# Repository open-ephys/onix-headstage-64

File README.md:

# ONIX 64-Channel Headstage
Serialized, multifunction headstage for wire electrode or silicon probe recordings.

- 64x electrophysiology channels
- 3x auxiliary analog channels (1x used by for stimulation current loop-back by
  default)
- 2x optical stimulation channels (LEDs or laser diodes; 800 mA per channel)
- 1x electrical stimulator (±2.5 mA, ±15V compliance; automatic discharge circuit)
- Integrated real-time, room-scale 3D-position tracking
- Integrated absolute orientation tracking

<br>
<br>

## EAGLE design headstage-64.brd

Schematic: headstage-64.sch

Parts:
C1: 0.1uF; 0201T; PARTNP CL03A104KA3NNNC
C2, C3, C5, C6, C18, C27, C32, C33, C35: 0.1uF; 0201T; PARTNO C0603X5R1C104K030BC
C4, C8, C9: 0.1uF; 0201T; PARTNO CL03A104KA3NNNC
C7: 4.7uF; 0402T; PARTNO CL05A475MO5NUNC
C10, C14, C15, C21, C22, C45, C51, C59, C66, C71: 10nF; 0201T
C11, C13, C16, C20, C23, C30, C31, C48: 0.1uF; 0201T
C12, C17: 4.7uF; 0402T; PARTNO GRM155R61A475MEAAD
C19, C28, C34, C36, C49: 1uF; 0201T; PARTNO CL03A105MP3ZSNH
C24: 15uF; 0402T; PARTNO CL05A226MQ5QUNC
C25: 0.1uF; 0201T; PARTNO C1005X7R1H104K050BB
C26: 47nF; 0201T; PARTNO C1005X7R1H473K050BB
C29: 10nF; 0201T; PARTNO GRM033R71E103KE14D
C37, C39, C41, C55, C69: 10uF; 0402T; PARTNO CL05A105KO5NNNC
C38, C40, C54, C56: 10uF; 0402T; PARTNO CL05A106MQ5NUNC
C42, C64: 0.22uF; 0402T; PARTNO UMK105BJ224KV-F
C43: 2.2nF; 0201T
C44, C50, C58, C65: 4.7nF; 0201T
C46, C52, C60, C67: 22nF; 0201T
C47, C61: 47nF; 0201T
C53, C62, C68: 0.47uF; 0201T; PARTNO GRM033R60J474KE90D
C57: 10pF; 0201T
C63, C72: 1uF; 0402T; PARTNO CL05A105KO5NNNC
C70: 4.7uF; 0402T; PARTNO CL05A105KO5NNNC
C73: 15uF; 0402T; PARTNO CL05A226MQ6ZUN8
C74, C75, C77: 10uF; 0402T; PARTNO CL05A475MO5NUNC
D4, D5, D6, D8: VEMD1160X01; 0805PT
D7: XZVGR155W; LED-0201T
D9: VSKY05401006; CLP1006-2L
J5: PINHD-1X4HEADSTAGE64_DAUGHTER-CARD; HEADSTAGE-64-DAUGHTER-CARD
J8: DF40C-70DP-0.4V(51); DF40-70HEAD-LESS-SILK
J9: PINHD-1X5_HALF_CONNECTOR; DF40-10HEAD_HALF
L2: BLM18KG601SN1D; 0603T
L4: CBC3225T101MR; 1210T
L6, L7, L8, L10: BLM15PX601SN1D; 0402T; PARTNO BLM15PX601SN1D
L9, L11: MLZ2012M100WT000; 0805T
L12: LQM21PN1R0NGRD; 0805T
R1: 9k, 0.1%; 0201T
R2: 1k, 0.1%; 0201T
R4, R5, R6, R7, R8, R11, R14, R16, R17, R18, R19: 10k, 0.1%; 0201T
R10, R21, R43: 1k; 0201T
R12, R31, R34, R35, R47: 100; 0201T
R13: 2.86k; 0201T
R15: 590; 0201T
R22, R23, R27, R28, R32, R33, R38, R39, R40, R49, R53, R54, R55, R56, R57: 10k; 0201T
R24, R26, R36, R42: 15k; 0201T
R25: 49.9; 0201T
R29: 0; 0201T
R30: 100k; 0201T
R37: 2k; 0201T
R41, R44, R51, R52: 4.7k; 0201T
R45, R50: 1M; 0201T
R46: 90.9k; 0201T
R48: 83.3k; 0201T
TP1, TP2, TP5, TP6: VCC; TP07R
TP3, TP4: TPTP09R; TP09R
TP7, TP8, TP9, TP10, TP11, TP12, TP13: TPTP06R; TP06R
TP14: gnd; TP06R
TP15: VCC; TP06R
U1: ADA4062-4ACPZ-R7; CP_16_27-L
U2: AD5681RBCPZ-1RL7; CP_8_10-L
U3: CAT4016_QFN; QFN24-4X4; PARTNO CAT4016HV6-GT2
U4: TPL0501_UQFN; UQFN; PARTNO TPL0501-100RSER
U5: DG509B; MQFN16-1.8X2.6
U6, U8, U11, U12: TS4231; WLCSP3X3
U7: RHD2064_BGA; BGA104_0.5MM
U9: DS90UB913A_WQFN; WQFN32-5X5
U10: BNO055; LGA-28-3.8X5.2
U13, U15: TLV70733; X2SON
U14: 10M08DC; VBGA81-4X4
U16: LT3463; DFN103X3
U17: TLV70725; X2SON
U18: TPS62621; XBGA6_1.2X0.8
U19: ASCO-50.000MHZ-EK-T3; ASCO
U20: TLV70712; X2SON

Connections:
!IMU_BL: R28.2, U10.4 (!BOOT_LOAD)
!IMU_RESET: R32.1, U10.11 (!RESET)
$N324: C50.1, C51.1, C52.1, C53.1, C54.1, L10.2, U14.A8 (VCCD_PLL2)
+1V2: C43.1, C44.1, C45.1, C46.1, C47.1, C48.1, C49.1, C73.1, L10.1, U14.B2 (VCC), U14.B9 (VCC), U14.H2 (VCC), U14.H8 (VCC), U20.1 (OUT)
+1V8: C13.1, C14.1, C15.1, C16.1, C17.1, C70.1, L6.1, L8.1, L12.1, R27.1, U9.11 (VDDT), U9.28 (VDDD), U18.C1 (FB)
+2V5: C56.1, C65.1, C66.1, C67.1, C68.1, C72.1, U14.B1 (VCCA3), U14.B8 (VCCA2), U14.J1 (VCCA1), U14.J9 (VCCA4), U17.1 (OUT), U20.3 (EN), U20.4 (IN)
+3V3: C3.1, C5.1, C18.1, C20.1, C21.1, C27.1, C31.1, C32.1, C35.1, C40.1, C58.1, C59.1, C60.1, C61.1, C62.1, C71.1, R22.1, R28.1, R32.2, R33.1, R37.1, R38.1, R39.1, R40.1, R41.2, R44.1, R51.2, R52.1, R53.1, R54.1, R55.1, R56.1, TP14.TP, U2.2 (VLOGIC), U4.7 (VDD), U6.C3 (DVDD), U8.C3 (DVDD), U9.25 (VDDIO), U10.3 (VDD), U10.28 (VDDIO), U11.C3 (DVDD), U12.C3 (DVDD), U14.D5 (VCCIO8), U14.E4 (VCCIO1_2), U14.E6 (VCCIO5_6), U14.F5 (VCCIO3), U15.1 (OUT), U19.1 (EN), U19.4 (VCC)
+3V3_AN: C30.2, C38.1, J9.4 (5), U7.M15 (VDD), U7.M16 (LVDS_EN), U7.N2 (VDD), U7.N15 (VDD), U13.1 (OUT)
+15V0: C1.1, C8.1, C42.1, R45.2, U1.3 (V+), U5.12 (V+), U16.1 (VOUT1)
-15V0: C4.1, C9.1, C57.2, C64.1, D9.A, R50.1, U1.10 (V-), U1.PAD (V-), U5.1 (V-)
AGND: C29.2, C30.1, C37.2, C38.2, J8.70, J8.M1, J8.M2, J8.M4, J9.M1 (1), J9.M2 (6), L7.2, R29.1, TP1.TP, U7.M2 (VESD), U7.M17 (GND), U7.N1 (GND), U7.N6 (GND), U13.2 (GND), U13.PAD (GND)
AUXIN2: J9.2 (3), TP6.TP, U7.N4 (AUXIN2)
AUXIN3: J9.1 (2), TP5.TP, U7.N3 (AUXIN1)
CONFIG_SEL: R57.1, U14.C6 (CONFIG_SEL/C6)
CONF_DONE: R56.2, U14.A2 (DIFFIO_RX_T24N/CONF_DONE/A2)
DAC_CS: U2.5 (!SYNC), U14.A5 (DIFFIO_RX_T18N/A5)
DATA1: U6.C1 (D/CFGDATA), U14.C7 (DIFFIO_RX_R33P/PLL_R_CLKOUTP/C7)
DATA2: U8.C1 (D/CFGDATA), U14.C3 (DIFFIO_RX_T26N/C3)
DATA3: U11.C1 (D/CFGDATA), U14.A7 (DIFFIO_RX_T16P/A7)
DATA4: U12.C1 (D/CFGDATA), U14.B6 (DIFFIO_RX_T16N/DEV_CLRN/B6)
DIN0: U9.19 (DIN0), U14.J6 (DIFFIO_TX_RX_B12P/J6)
DIN1: U9.20 (DIN1), U14.G6 (DIFFIO_TX_RX_B14N/G6)
DIN2: U9.21 (DIN2), U14.H7 (DIFFIO_TX_RX_B14P/H7)
DIN3: U9.22 (DIN3), U14.J7 (DIFFIO_TX_RX_B16N/J7)
DIN4: U9.23 (DIN4), U14.G8 (DIFFIO_RX_R7P/G8)
DIN5: U9.24 (DIN5), U14.G9 (DIFFIO_RX_R7N/G9)
DIN6: U9.26 (DIN6), U14.F7 (DIFFIO_RX_R1N/F7)
DIN7: U9.27 (DIN7), U14.E7 (DIFFIO_RX_R14N/CLK2N/E7)
DIN8: U9.29 (DIN8), U14.E8 (DIFFIO_RX_R14P/CLK2P/E8)
DIN9: U9.30 (DIN9), U14.C8 (DIFFIO_RX_R27P/C8)
DIN10: U9.31 (DIN10), U14.C5 (CRC_ERROR/C5)
DIN11: U9.32 (DIN11), U14.C4 (DIFFIO_RX_T26P/C4)
E0: J8.2, U7.K2 (IN0)
E1: J8.68, U7.J1 (IN1)
E2: J8.3, U7.J2 (IN2)
E3: J8.67, U7.H1 (IN3)
E4: J8.4, U7.H2 (IN4)
E5: J8.66, U7.G1 (IN5)
E6: J8.5, U7.G2 (IN6)
E7: J8.65, U7.F1 (IN7)
E8: J8.6, U7.F2 (IN8)
E9: J8.64, U7.E1 (IN9)
E10: J8.7, U7.E2 (IN10)
E11: J8.63, U7.D1 (IN11)
E12: J8.8, U7.D2 (IN12)
E13: J8.62, U7.C1 (IN13)
E14: J8.9, U7.C2 (IN14)
E15: J8.61, U7.B1 (IN15)
E16: J8.10, U7.A1 (IN16)
E17: J8.60, U7.B2 (IN17)
E18: J8.11, U7.A2 (IN18)
E19: J8.59, U7.B3 (IN19)
E20: J8.12, U7.A3 (IN20)
E21: J8.58, U7.B4 (IN21)
E22: J8.13, U7.A4 (IN22)
E23: J8.57, U7.B5 (IN23)
E24: J8.14, U7.A5 (IN24)
E25: J8.56, U7.B6 (IN25)
E26: J8.15, U7.A6 (IN26)
E27: J8.55, U7.B7 (IN27)
E28: J8.16, U7.A7 (IN28)
E29: J8.54, U7.B8 (IN29)
E30: J8.17, U7.A8 (IN30)
E31: J8.53, U7.B9 (IN31)
E32: J8.18, U7.A9 (IN32)
E33: J8.52, U7.A10 (IN33)
E34: J8.19, U7.B10 (IN34)
E35: J8.51, U7.A11 (IN35)
E36: J8.20, U7.B11 (IN36)
E37: J8.50, U7.A12 (IN37)
E38: J8.21, U7.B12 (IN38)
E39: J8.49, U7.A13 (IN39)
E40: J8.22, U7.B13 (IN40)
E41: J8.48, U7.A14 (IN41)
E42: J8.23, U7.B14 (IN42)
E43: J8.47, U7.A15 (IN43)
E44: J8.24, U7.B15 (IN44)
E45: J8.46, U7.A16 (IN45)
E46: J8.25, U7.B16 (IN46)
E47: J8.45, U7.A17 (IN47)
E48: J8.26, U7.B17 (IN48)
E49: J8.44, U7.C16 (IN49)
E50: J8.27, U7.C17 (IN50)
E51: J8.43, U7.D16 (IN51)
E52: J8.28, U7.D17 (IN52)
E53: J8.42, U7.E16 (IN53)
E54: J8.29, U7.E17 (IN54)
E55: J8.41, U7.F16 (IN55)
E56: J8.30, U7.F17 (IN56)
E57: J8.40, U7.G16 (IN57)
E58: J8.31, U7.G17 (IN58)
E59: J8.39, U7.H16 (IN59)
E60: J8.32, U7.H17 (IN60)
E61: J8.38, U7.J16 (IN61)
E62: J8.33, U7.J17 (IN62)
E63: J8.37, U7.K16 (IN63)
ENV1: U6.C2 (E/CFGCLK), U14.B5 (DIFFIO_RX_T19N/B5)
ENV2: U8.C2 (E/CFGCLK), U14.C2 (DIFFIO_RX_L1N/C2)
ENV3: U11.C2 (E/CFGCLK), U14.D9 (DIFFIO_RX_R16N/CLK3N/D9)
ENV4: U12.C2 (E/CFGCLK), U14.B7 (DIFFIO_RX_R33N/PLL_R_CLKOUTN/B7)
ESTIM_POW_EN: R49.1, U14.A6 (DIFFIO_RX_T18P/DEV_OE/A6), U16.8 (!SHDN2), U16.9 (!SHDN1)
GND: C1.2, C2.2, C3.2, C4.2, C5.2, C6.2, C7.2, C8.2, C9.2, C10.2, C11.2, C12.2, C13.2, C14.2, C15.2, C16.2, C17.2, C18.2, C19.2, C20.2, C21.2, C22.2, C23.2, C24.2, C27.2, C28.2, C31.2, C32.2, C33.1, C34.2, C35.2, C36.2, C39.2, C40.2, C41.2, C42.2, C43.2, C44.2, C45.2, C46.2, C47.2, C48.2, C49.2, C50.2, C51.2, C52.2, C53.2, C54.2, C55.2, C56.2, C58.2, C59.2, C60.2, C61.2, C62.2, C64.2, C65.2, C66.2, C67.2, C68.2, C69.2, C70.2, C71.2, C72.2, C73.2, C74.2, C75.2, C77.2, J5.2, J5.4, L7.1, R19.1, R21.1, R23.2, R24.1, R25.1, R26.1, R30.2, R36.1, R42.1, R43.2, R46.1, R49.2, R57.2, TP3.TP, TP15.TP, U2.3 (GND), U2.PAD (GND), U3.1 (GND), U3.PAD (GND), U4.4 (GND), U4.8 (LA), U5.2 (X0), U5.13 (GND), U5.14 (B), U6.B2 (AVSS), U6.B3 (AVSS2), U8.B2 (AVSS), U8.B3 (AVSS2), U9.6 (ID), U9.7 (RES), U9.PAD (GND), U10.2 (GND), U10.5 (PS1), U10.6 (PS0), U10.15 (GNDIO), U10.16 (GNDIO), U10.17 (COM3/ADDR), U10.18 (COM2), U10.25 (GNDIO), U11.B2 (AVSS), U11.B3 (AVSS2), U12.B2 (AVSS), U12.B3 (AVSS2), U14.A1 (GND), U14.A9 (GND), U14.B4 (GND), U14.D1 (GND), U14.D7 (GND), U14.E5 (GND), U14.E9 (GND), U14.F4 (GND), U14.F6 (GND), U14.H1 (GND), U14.H5 (GND), U14.H9 (GND), U15.2 (GND), U15.PAD (GND), U16.PAD (GND), U17.2 (GND), U17.PAD (GND), U18.C2 (GND), U19.2 (GND), U20.2 (GND), U20.PAD (GND)
GPIO0: J9.3 (4), TP4.TP, U9.15 (GPIO0), U14.A3
GPIO1: U9.16 (GPIO1), U14.H6 (DIFFIO_TX_RX_B12N/H6)
HSYNC: U9.1 (HSYNC), U14.F2 (DIFFIO_RX_L18P/CLK0P/F2)
IMU_INT: U10.14 (INT)
IMU_SCL: R41.1, U10.19 (COM1/SCL/RX), U14.E3
IMU_SDA: R51.1, U10.20 (COM0/SDA/TX), U14.F9 (DIFFIO_RX_R10N/F9)
ISTIM: J8.1, U5.6 (X), U5.10 (Y1)
ISTIM_MONO: R14.1, R19.2, U7.N5 (AUXIN3)
ISTIM_PRE: R12.1, U1.9 (+IN), U5.7 (Y)
JTAGEN: R38.2, U14.D2 (JTAGEN/D2)
LED-1: J8.34, U3.5 (LED1), U3.6 (LED2), U3.7 (LED3), U3.8 (LED4), U3.9 (LED5), U3.10 (LED6), U3.11 (LED7), U3.12 (LED8)
LED-2: J8.35, U3.13 (LED9), U3.14 (LED10), U3.15 (LED11), U3.16 (LED12), U3.17 (LED13), U3.18 (LED14), U3.19 (LED15), U3.20 (LED16)
LED_BLANK: R53.2, U3.21 (BLANK), U14.C9 (DIFFIO_RX_R27N/C9)
LED_LATCH: U3.4 (LATCH), U14.J8 (DIFFIO_TX_RX_B16P/J8)
MIDFILT: J5.1, L4.1, R10.1
MOSI: U2.6 (DIN), U3.2 (SIN), U4.2 (DIN), U14.A4 (DIFFIO_RX_T19P/A4)
unnamed: R15.2, U4.6 (WA)
unnamed: C63.1, L11.1, U16.4 (SW2)
unnamed: C57.1, R48.1, R50.2, U16.6 (FB2)
unnamed: D4.C, U6.A3 (IIN-)
unnamed: D4.A, U6.A2 (IIN+)
unnamed: R24.2, U6.B1 (RBIAS)
unnamed: C19.1, U6.A1 (AVDD)
unnamed: L9.1, U16.2 (SW1)
unnamed: D5.C, U8.A3 (IIN-)
unnamed: D5.A, U8.A2 (IIN+)
unnamed: R26.2, U8.B1 (RBIAS)
unnamed: C28.1, U8.A1 (AVDD)
unnamed: C6.1, C7.1, L2.1, L4.2, R10.2
unnamed: R15.1, U3.23 (RSET)
unnamed: D6.C, U11.A3 (IIN-)
unnamed: D6.A, U11.A2 (IIN+)
unnamed: R36.2, U11.B1 (RBIAS)
unnamed: C34.1, U11.A1 (AVDD)
unnamed: C63.2, D9.C, U16.5 (D2)
unnamed: R1.2, R2.2, R12.2, U1.4 (+IN)
unnamed: R21.2, U5.11 (Y0)
unnamed: R45.1, R46.2, U16.10 (FB1)
unnamed: D8.C, TP7.TP, U12.A3 (IIN-)
unnamed: R48.2, U16.7 (VREF)
unnamed: C25.2, U9.13 (DOUT+)
unnamed: D7.2 (A), R37.2
unnamed: R33.2, U9.9 (PDB)
unnamed: C26.2, U9.12 (DOUT-)
unnamed: C26.1, R25.2
unnamed: R27.2, R30.1, U9.8 (MODE)
unnamed: C10.1, C11.1, C12.1, L6.2, U9.10 (VDDPLL)
unnamed: C22.1, C23.1, C24.1, L8.2, U9.14 (VDDCML)
unnamed: C29.1, U7.N17 (ADC_REF)
unnamed: U14.D8 (DIFFIO_RX_R16P/CLK3P/D8), U19.3 (OUT)
unnamed: D8.A, TP8.TP, U12.A2 (IIN+)
unnamed: TP2.TP, U7.N16 (AUXOUT)
unnamed: R42.2, U12.B1 (RBIAS)
unnamed: C36.1, U12.A1 (AVDD)
unnamed: R22.2, U5.16 (EN)
unnamed: R54.2, U14.D6 (NCONFIG/D6)
unnamed: L12.2, U18.B1 (SW)
unnamed: R1.1, R4.2, U1.2 (+IN)
unnamed: R5.2, R11.1, U1.1 (-IN)
unnamed: R2.1, R11.2, U1.15 (OUT)
unnamed: R16.1, R17.2, U1.6 (OUT)
unnamed: R13.1, R16.2, U1.5 (-IN)
unnamed: R8.1, R13.2, U1.8 (-IN)
unnamed: R6.2, R8.2, U1.7 (OUT)
unnamed: R7.1, R14.2, U1.14 (OUT)
unnamed: R6.1, R7.2, U1.12 (-IN)
unnamed: R17.1, R18.2, U1.11 (+IN)
unnamed: C33.2, U10.9 (CAP)
NSTATUS: R55.2, U14.B3 (DIFFIO_RX_T24P/NSTATUS/B3)
PCLK: U9.3 (PCLK1), U14.G2 (DIFFIO_RX_L20N/CLK1N/G2)
POT_CS: U4.3 (!CS), U14.G7 (DIFFIO_RX_R1P/G7)
REF: J8.69, R29.2, U7.M1 (REF_ELEC)
RHD_CLK_N: R34.1, U7.N9 (SCLK-), U14.G5 (DIFFIO_TX_RX_B3P/G5)
RHD_CLK_P: R34.2, U7.N10 (SCLK+), U14.G4 (DIFFIO_TX_RX_B3N/G4)
RHD_CS_N: R31.1, U7.N7 (!CS!-), U14.J2 (DIFFIO_TX_RX_B1P/J2)
RHD_CS_P: R31.2, U7.N8 (!CS!+), U14.H3 (DIFFIO_TX_RX_B1N/H3)
RHD_MISO_N: R47.1, U7.N13 (MISO-), U14.J5 (DIFFIO_TX_RX_B9P/J5)
RHD_MISO_P: R47.2, U7.N14 (MISO+), U14.J4 (DIFFIO_TX_RX_B9N/J4)
RHD_MOSI_N: R35.1, U7.N11 (MOSI-), U14.H4 (DIFFIO_TX_RX_B5P/H4)
RHD_MOSI_P: R35.2, U7.N12 (MOSI+), U14.J3 (DIFFIO_TX_RX_B5N/J3)
SCL: R44.2, U9.4 (SCL), U14.G3 (DIFFIO_RX_L27P/G3)
SCLK: U2.4 (SCLK), U3.3 (CLK), U4.5 (SCLK), U14.F3 (DIFFIO_RX_L27N/F3)
SDA: R52.2, U9.5 (SDA), U14.F8 (DIFFIO_RX_R10P/F8)
SIGOUT: C25.1, J5.3
STATUS: D7.1 (C), U14.C1 (DIFFIO_RX_L1P/C1)
STIM_NULL: R23.1, U5.15 (A), U14.F1 (DIFFIO_RX_L18N/CLK0N/F1)
TCK: R43.1, TP11.TP, U14.D4 (DIFFIO_RX_L11P/TCK/D4)
TDI: R40.2, TP12.TP, U14.E1 (DIFFIO_RX_L12N/TDI/E1)
TDO: TP13.TP, U14.E2 (DIFFIO_RX_L12P/TDO/E2)
TMS: R39.2, TP10.TP, U14.D3 (DIFFIO_RX_L11N/TMS/D3)
VCOAX: C2.1, C37.1, C39.1, C41.1, C55.1, C69.1, C74.1, C75.1, C77.1, J8.36, J8.M3, L2.2, L9.2, L11.2, TP9.TP, U2.1 (AVDD), U3.24 (VDD), U13.3 (EN), U13.4 (IN), U15.3 (EN), U15.4 (IN), U16.3 (VIN), U17.3 (EN), U17.4 (IN), U18.A1 (MODE), U18.A2 (VIN), U18.B2 (EN)
VDAC: R4.1, U2.8 (VOUT)
VREF_2V5: R5.1, R18.1, U2.7 (VREF)
VSYNC: U9.2 (VSYNC), U14.G1 (DIFFIO_RX_L20P/CLK1P/G1)

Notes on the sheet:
NB: Inductors pass 250mA DC max before they are used to generate a flyback voltage. Because we are dealing with a very low current application, we can probably get away with inductors that saturate below 250 mA so long as they are capable of handling the current. The MLZ2012M100WT000 saturates at 2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
NB: VCoax must NOT exceed 5.5V
Programming interface
ESTIM
OPTOSTIM
SERIALIZER
FPGA
ADC
TRACKING
POWER
NB: Because we are suing a 3.3V IO voltage for bank 3, the LVDS produced here is technically out of spec. The lines sit at 1.6V and swing about 600 mV. This is a result of using 3.3V supply on an FPGA that nominally requires a 2.5 rail to get LVDS to its standard 1.2V common mode voltage with 400 m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
DNP
NB: CLK3 drives PLL2
NB: ISTIM = (VDAC - 2.5)/1000. e.g. VDAC = 2.5 -> ISTIM = 0 VDAC = 5.0 -> ISTIM = 2.5 mA VDAC = 0.0 -> ISTIM = -2.5mA and Imeas = 400 * ISTIM + 1.25V e.g. ISTIM = 0 -> IMEAS = 1.25V ISTIM = 2.5mA -> IMEAS = 2.25V ISTIM = -2.5mA -> IMEAS = 0.25V
I2C Selected
NB To get the best performance out of BNO055, it is recommended to use the external 32.768 kHz crystal.
NB: Decoupling relies on input caps for the LDO regulators.
ADAPTER INPUT

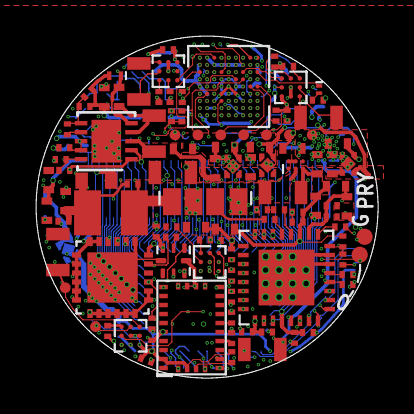
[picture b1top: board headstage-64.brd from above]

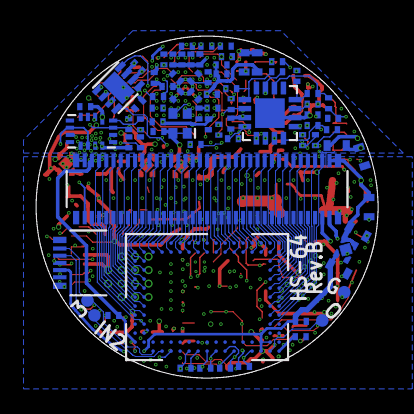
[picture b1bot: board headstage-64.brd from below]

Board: 8 copper layers, 19.0 x 19.0 mm, 183 parts (77 on the bottom side), 195 nets.

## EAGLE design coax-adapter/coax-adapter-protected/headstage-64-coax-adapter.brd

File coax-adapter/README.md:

# Coaxial Cable Module
This small board has castellated edge contacts and is soldered onto the
headstage's center contacts to provide coax IO. It contains a portion of the
power conditioning circuit on the main board and is therefore necessary for
headstage operation. There are two variants:

1. coax-adapter-protected (recommended)
    - Contains over/under-voltage lockout circuit that ensures unregulated
      input voltage will not damage headstage but requires that the user tune
      the power supply to account for cable voltage drop
    - Has extra bulk capacitance, which reduces noise
1. coax-adapter-regulated
    - Contains a step-down regulator that ensures proper 5.5V supply to the
      headstage so long as input voltage is greater than 5.5V
    - Has less bulk capacitance and switching supply may introduce noise

## Bill of Materials
The bill of materials for this device can be found
[here](https://docs.google.com/spreadsheets/d/1pUGBYAdJs2eZZaEnTpPPK72m9BNobIhAjmIrxtYpmq0/edit?usp=sharing).

## Manufacturing Requirements
This PCB has the following requirements:

- 4 copper layers
- 0.6 mm (or thinner) total thickness
- Castellated edge contacts

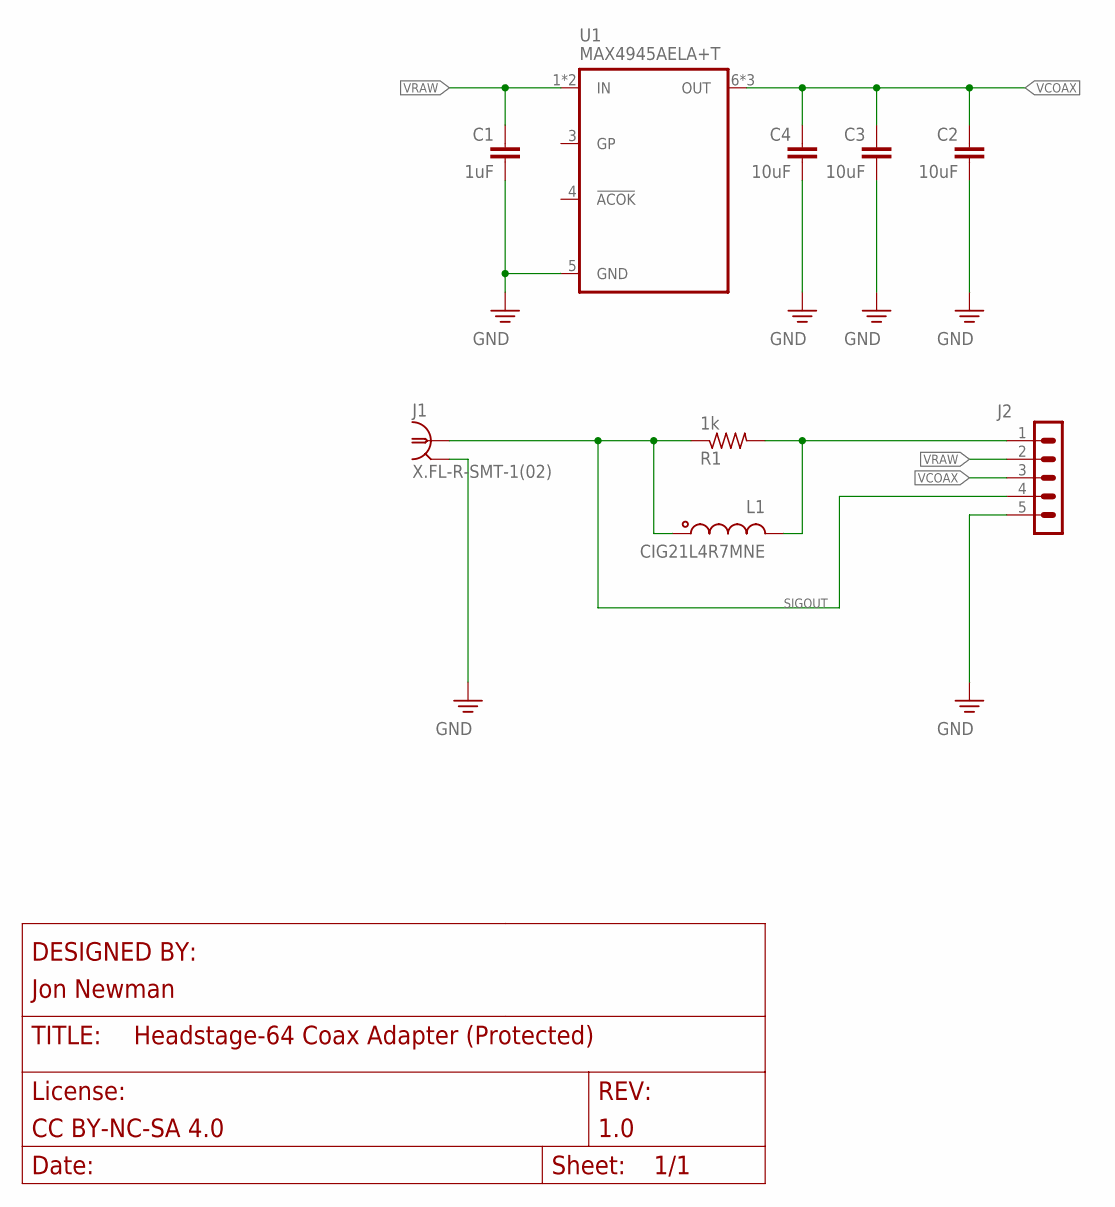
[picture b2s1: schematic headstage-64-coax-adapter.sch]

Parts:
C1: 1uF; 0402T; PARTNO CL05A475MO5NUNC
C2: 10uF; 0402T; PARTNO CL05A475MO5NUNC
C3, C4: 10uF; 0603T; PARTNO CL05A475MO5NUNC
J1: X.FL-R-SMT-1(02); X_FL_R_SMT_1(02)
J2: PINHD-1X5_HEADSTAGE-64-REV1.4-DAUGHTER-CARD-CASTE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; HEADSTAGE-64-REV1.4-DAUGHTER-CARD-CASTELLATED
L1: CIG21L4R7MNE; 0805T
R1: 1k; 0201T
U1: MAX4945AELA+T; UDFN8-2X2

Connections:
GND: C1.2, C2.2, C3.2, C4.2, J1.P$2 (2), J1.P$3 (2), J1.P$4 (2), J2.5, U1.5 (GND)
unnamed: J2.1, L1.2, R1.2
SIGOUT: J1.P$1 (1), J2.4, L1.1, R1.1
VCOAX: C2.1, C3.1, C4.1, J2.3, U1.6 (OUT), U1.7 (OUT), U1.8 (OUT)
VRAW: C1.1, J2.2, U1.1 (IN), U1.2 (IN)

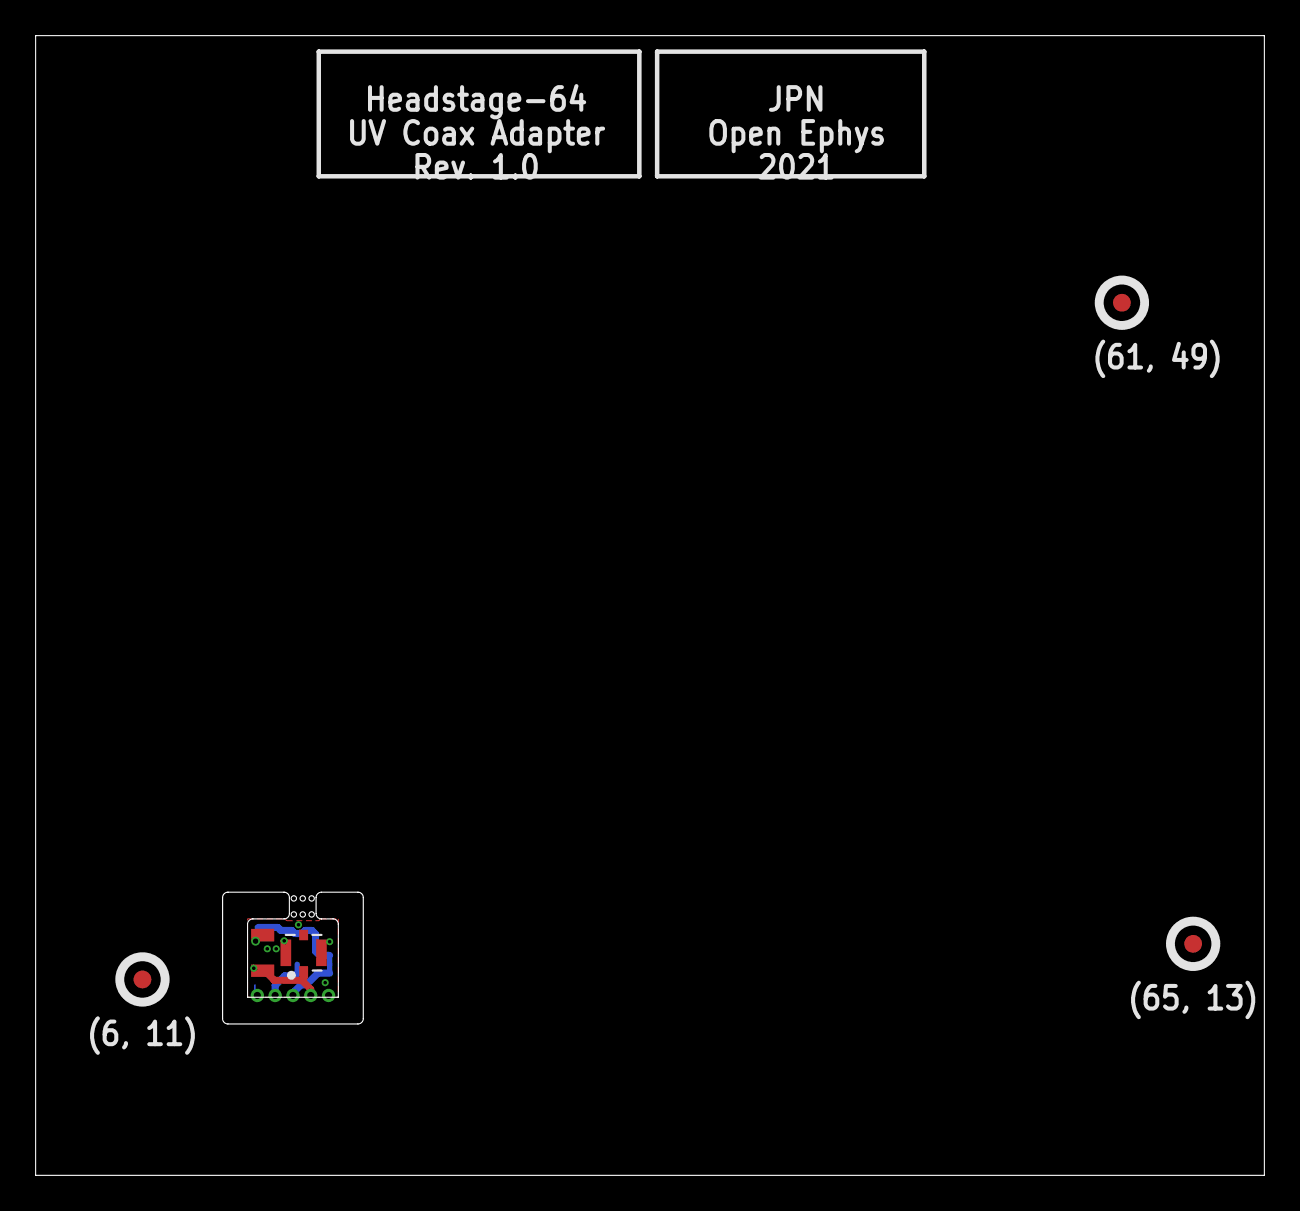
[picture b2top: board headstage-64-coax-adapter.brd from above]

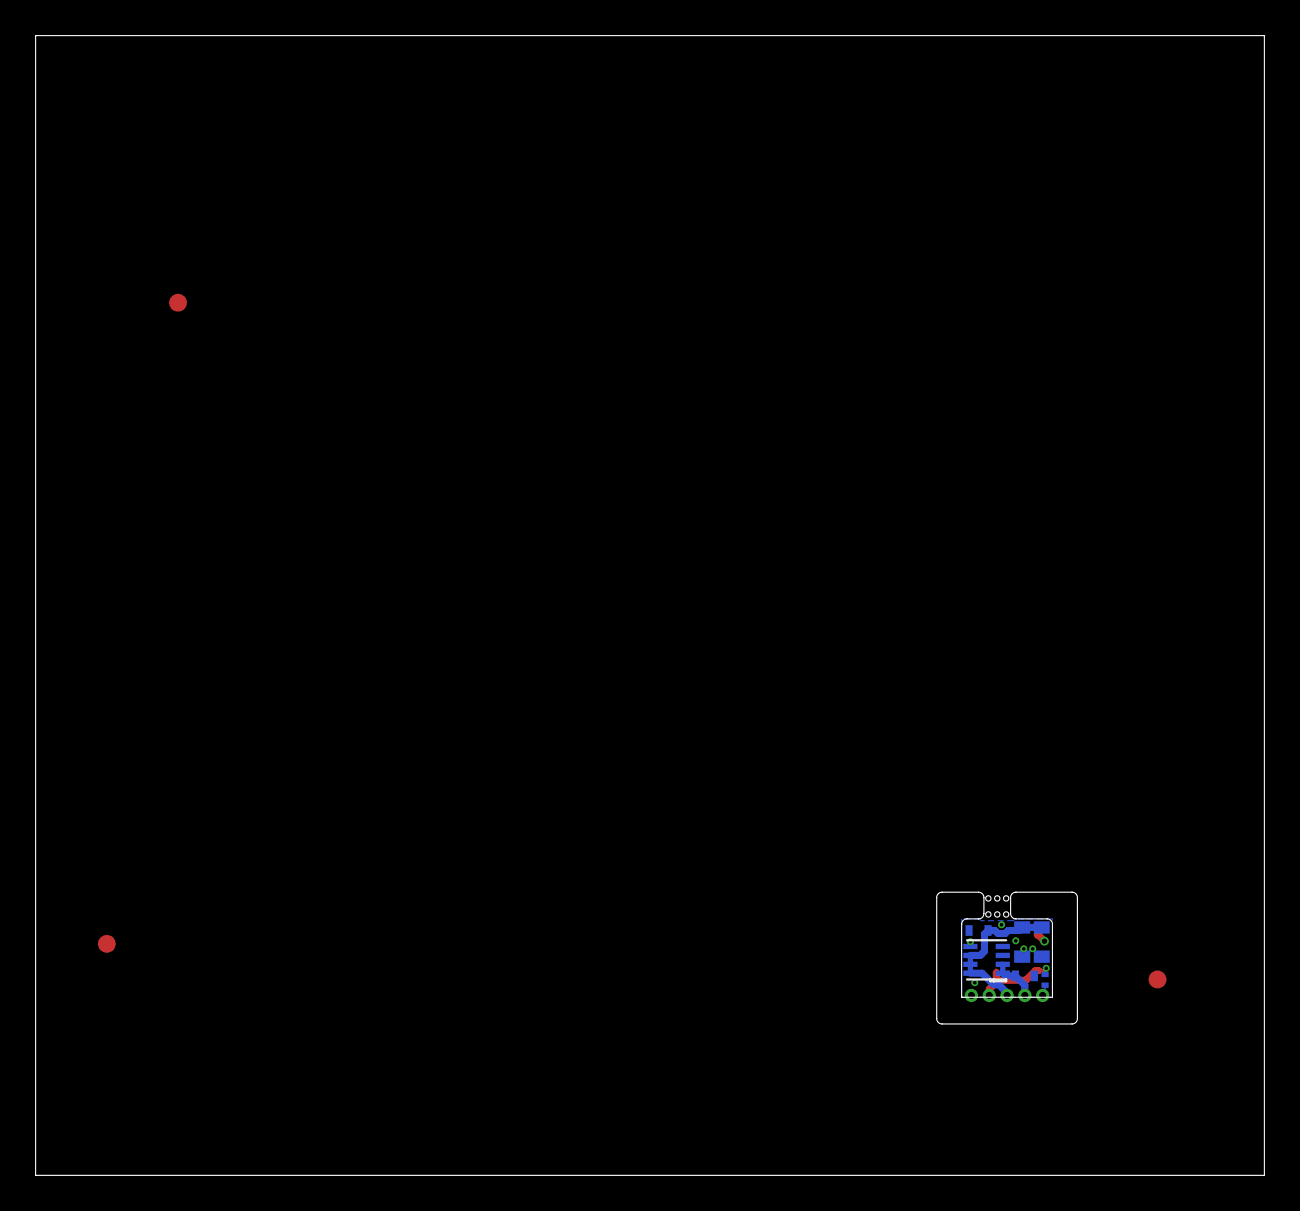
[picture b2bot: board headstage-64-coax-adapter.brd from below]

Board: 4 copper layers, 69.0 x 64.0 mm, 12 parts (6 on the bottom side), 5 nets.

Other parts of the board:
E$1, E$2, E$4: FIDUCIAL

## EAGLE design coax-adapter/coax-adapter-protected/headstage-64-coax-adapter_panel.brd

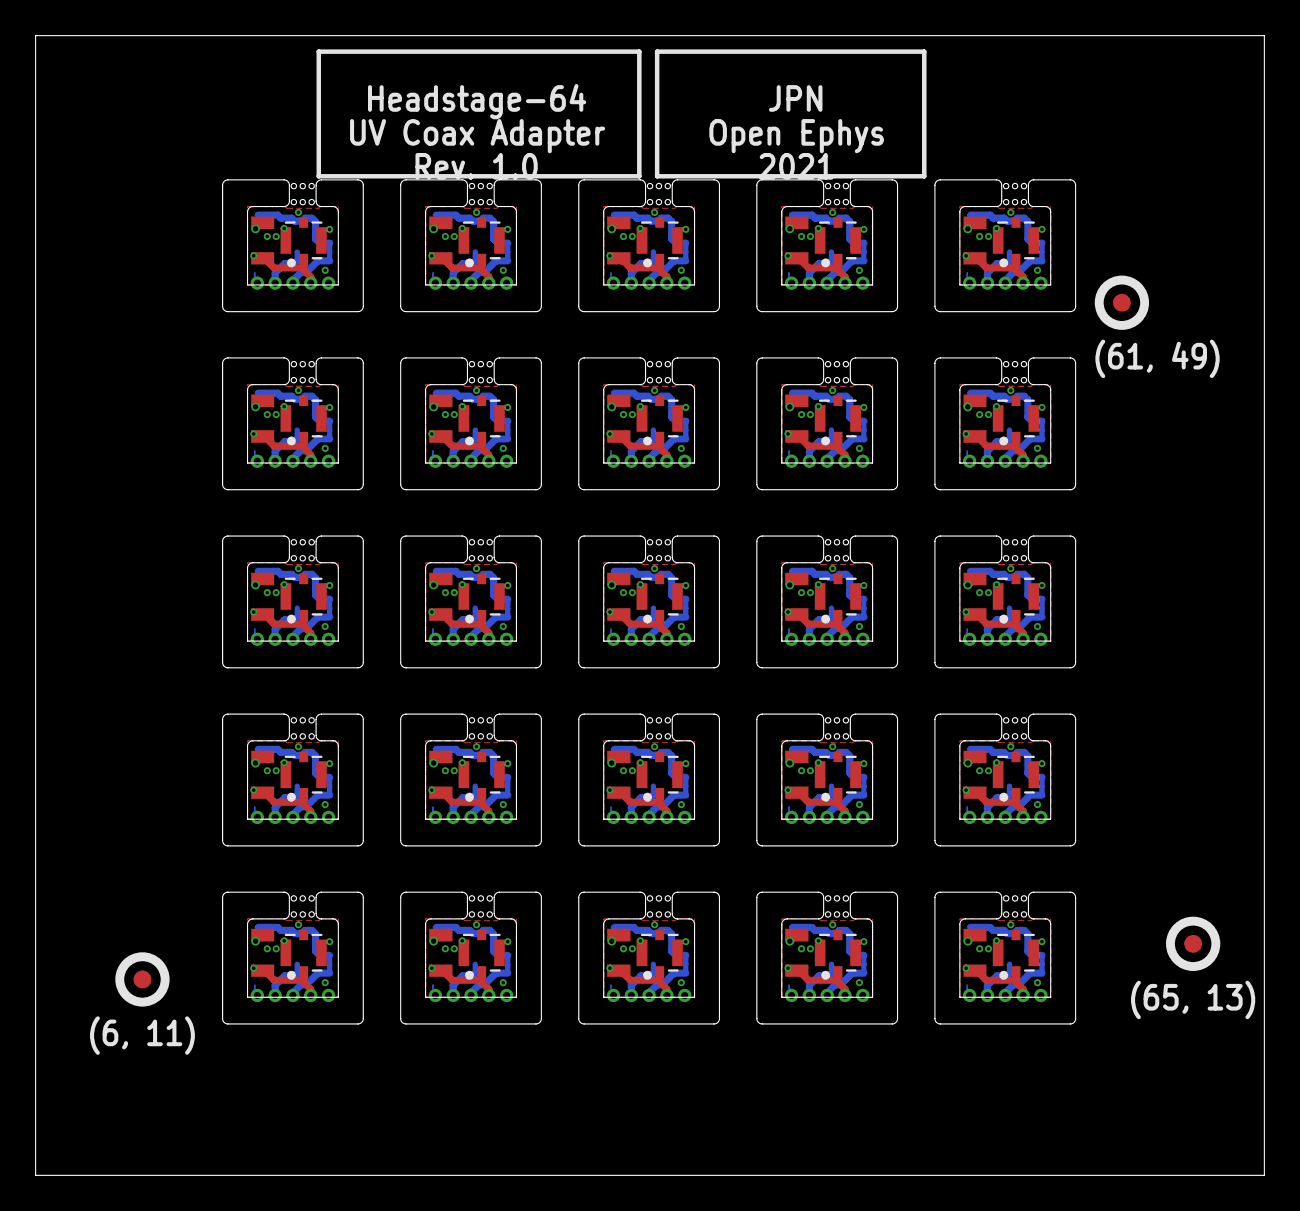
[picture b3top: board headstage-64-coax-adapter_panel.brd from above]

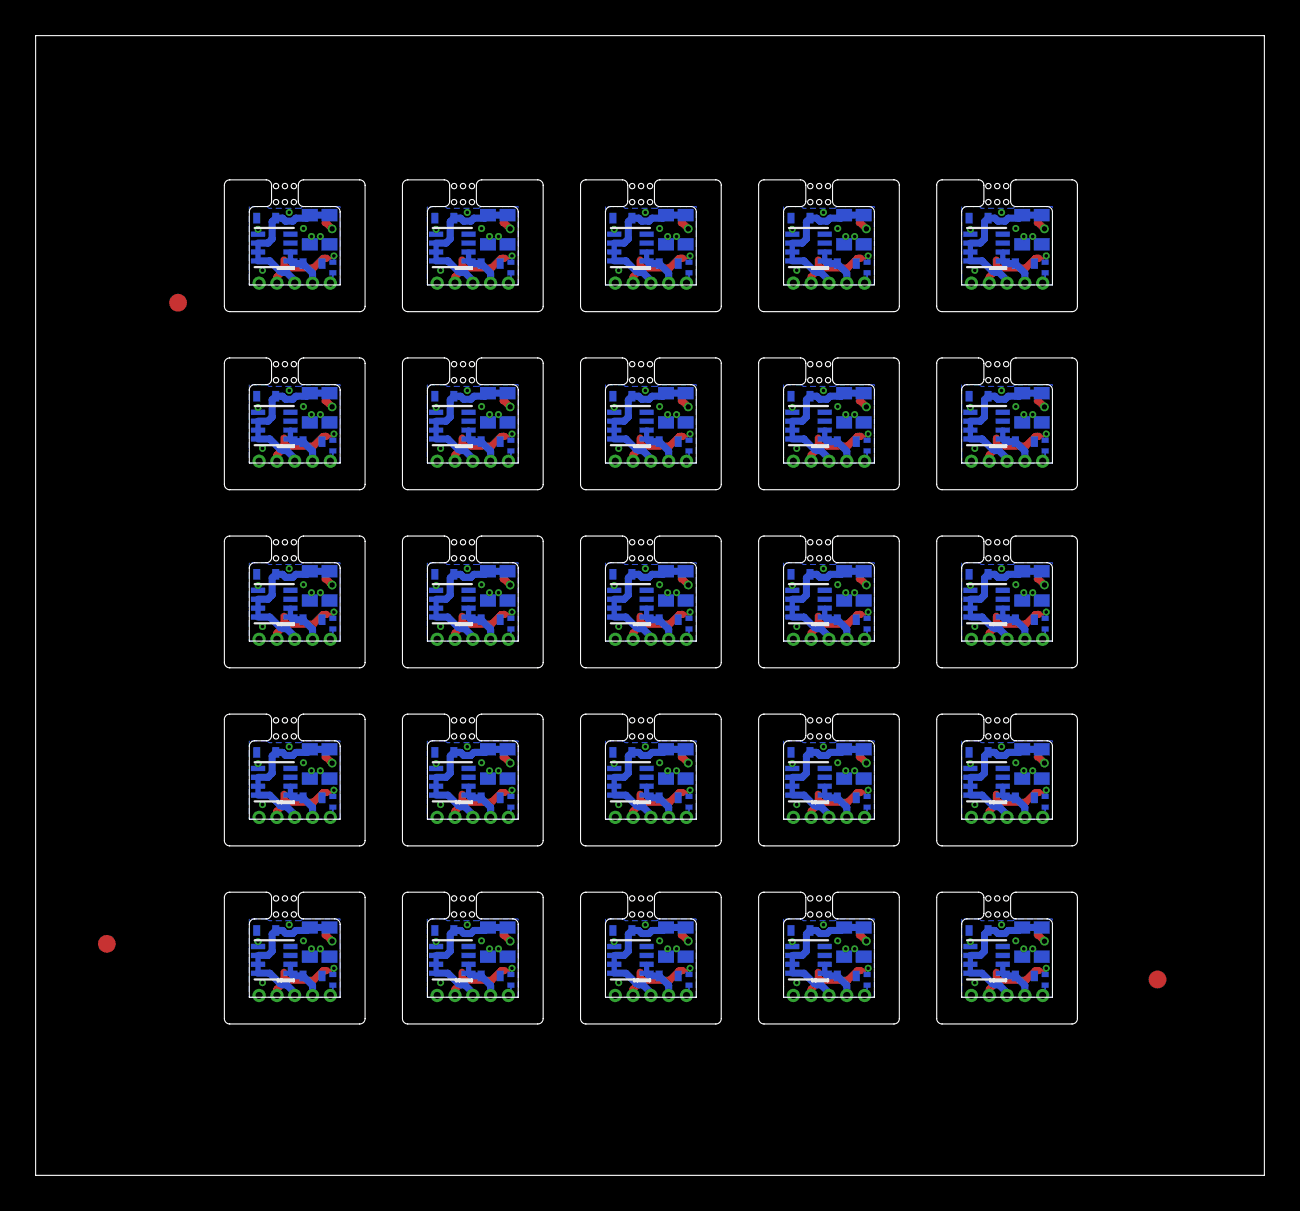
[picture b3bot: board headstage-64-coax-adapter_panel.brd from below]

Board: 4 copper layers, 69.0 x 64.0 mm, 228 parts (150 on the bottom side), 125 nets.

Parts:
C1, C6, C10, C14, C18, C22, C26, C30, C34, C38, C42, C46, C50, C54, C58, C62, C66, C70, C74, C78, C82, C86, C90, C94, C98: 1uF; 0402T
C2, C5, C9, C13, C17, C21, C25, C29, C33, C37, C41, C45, C49, C53, C57, C61, C65, C69, C73, C77, C81, C85, C89, C93, C97: 10uF; 0402T
C3, C4, C7, C8, C11, C12, C15, C16, C19, C20, C23, C24, C27, C28, C31, C32, C35, C36, C39, C40, C43, C44, C47, C48, C51, C52, C55, C56, C59, C60, C63, C64, C67, C68, C71, C72, C75, C76, C79, C80, C83, C84, C87, C88, C91, C92, C95, C96, C99, C100: 10uF; 0603T
E$1, E$2, E$4: FIDUCIAL
J1, J3, J5, J7, J9, J11, J13, J15, J17, J19, J21, J23, J25, J27, J29, J31, J33, J35, J37, J39, J41, J43, J45, J47, J49: X.FL-R-SMT-1(02); X_FL_R_SMT_1(02)
J2, J4, J6, J8, J10, J12, J14, J16, J18, J20, J22, J24, J26, J28, J30, J32, J34, J36, J38, J40, J42, J44, J46, J48, J50: HEADSTAGE-64-REV1.4-DAUGHTER-CARD-CASTELLATED
L1, L2, L3, L4, L5, L6, L7, L8, L9, L10, L11, L12, L13, L14, L15, L16, L17, L18, L19, L20, L21, L22, L23, L24, L25: CIG21L4R7MNE; 0805T
R1, R2, R3, R4, R5, R6, R7, R8, R9, R10, R11, R12, R13, R14, R15, R16, R17, R18, R19, R20, R21, R22, R23, R24, R25: 1k; 0201T
U1, U2, U3, U4, U5, U6, U7, U8, U9, U10, U11, U12, U13, U14, U15, U16, U17, U18, U19, U20, U21, U22, U23, U24, U25: MAX4945AELA+T; UDFN8-2X2

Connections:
GND: C1.2, C2.2, C3.2, C4.2, J1.P$2, J1.P$3, J1.P$4, J2.5, U2.5
GND2: C5.2, C6.2, C7.2, C8.2, J3.P$2, J3.P$3, J3.P$4, J4.5, U1.5
GND10: C9.2, C10.2, C11.2, C12.2, J5.P$2, J5.P$3, J5.P$4, J6.5, U3.5
GND12: C13.2, C14.2, C15.2, C16.2, J7.P$2, J7.P$3, J7.P$4, J8.5, U4.5
GND14: C17.2, C18.2, C19.2, C20.2, J9.P$2, J9.P$3, J9.P$4, J10.5, U5.5
GND16: C21.2, C22.2, C23.2, C24.2, J11.P$2, J11.P$3, J11.P$4, J12.5, U6.5
GND18: C25.2, C26.2, C27.2, C28.2, J13.P$2, J13.P$3, J13.P$4, J14.5, U7.5
GND20: C29.2, C30.2, C31.2, C32.2, J15.P$2, J15.P$3, J15.P$4, J16.5, U8.5
GND22: C33.2, C34.2, C35.2, C36.2, J17.P$2, J17.P$3, J17.P$4, J18.5, U9.5
GND24: C37.2, C38.2, C39.2, C40.2, J19.P$2, J19.P$3, J19.P$4, J20.5, U10.5
GND26: C41.2, C42.2, C43.2, C44.2, J21.P$2, J21.P$3, J21.P$4, J22.5, U11.5
GND28: C45.2, C46.2, C47.2, C48.2, J23.P$2, J23.P$3, J23.P$4, J24.5, U12.5
GND30: C49.2, C50.2, C51.2, C52.2, J25.P$2, J25.P$3, J25.P$4, J26.5, U13.5
GND32: C53.2, C54.2, C55.2, C56.2, J27.P$2, J27.P$3, J27.P$4, J28.5, U14.5
GND34: C57.2, C58.2, C59.2, C60.2, J29.P$2, J29.P$3, J29.P$4, J30.5, U15.5
GND36: C61.2, C62.2, C63.2, C64.2, J31.P$2, J31.P$3, J31.P$4, J32.5, U16.5
GND38: C65.2, C66.2, C67.2, C68.2, J33.P$2, J33.P$3, J33.P$4, J34.5, U17.5
GND40: C69.2, C70.2, C71.2, C72.2, J35.P$2, J35.P$3, J35.P$4, J36.5, U18.5
GND42: C73.2, C74.2, C75.2, C76.2, J37.P$2, J37.P$3, J37.P$4, J38.5, U19.5
GND44: C77.2, C78.2, C79.2, C80.2, J39.P$2, J39.P$3, J39.P$4, J40.5, U20.5
GND45: C81.2, C82.2, C83.2, C84.2, J41.P$2, J41.P$3, J41.P$4, J42.5, U21.5
GND46: C85.2, C86.2, C87.2, C88.2, J43.P$2, J43.P$3, J43.P$4, J44.5, U22.5
GND47: C89.2, C90.2, C91.2, C92.2, J45.P$2, J45.P$3, J45.P$4, J46.5, U23.5
GND48: C93.2, C94.2, C95.2, C96.2, J47.P$2, J47.P$3, J47.P$4, J48.5, U24.5
GND49: C97.2, C98.2, C99.2, C100.2, J49.P$2, J49.P$3, J49.P$4, J50.5, U25.5
unnamed: J4.1, L2.2, R2.2
unnamed: J6.1, L3.2, R3.2
unnamed: J8.1, L4.2, R4.2
unnamed: J10.1, L5.2, R5.2
unnamed: J12.1, L6.2, R6.2
unnamed: J14.1, L7.2, R7.2
unnamed: J16.1, L8.2, R8.2
unnamed: J18.1, L9.2, R9.2
unnamed: J20.1, L10.2, R10.2
unnamed: J22.1, L11.2, R11.2
unnamed: J24.1, L12.2, R12.2
unnamed: J26.1, L13.2, R13.2
unnamed: J28.1, L14.2, R14.2
unnamed: J30.1, L15.2, R15.2
unnamed: J32.1, L16.2, R16.2
unnamed: J34.1, L17.2, R17.2
unnamed: J36.1, L18.2, R18.2
unnamed: J38.1, L19.2, R19.2
unnamed: J40.1, L20.2, R20.2
unnamed: J42.1, L21.2, R21.2
unnamed: J44.1, L22.2, R22.2
unnamed: J46.1, L23.2, R23.2
unnamed: J48.1, L24.2, R24.2
unnamed: J50.1, L25.2, R25.2
unnamed: J2.1, L1.2, R1.2
SIGOUT: J1.P$1, J2.4, L1.1, R1.1
SIGOUT1: J3.P$1, J4.4, L2.1, R2.1
SIGOUT2: J5.P$1, J6.4, L3.1, R3.1
SIGOUT3: J7.P$1, J8.4, L4.1, R4.1
SIGOUT4: J9.P$1, J10.4, L5.1, R5.1
SIGOUT5: J11.P$1, J12.4, L6.1, R6.1
SIGOUT6: J13.P$1, J14.4, L7.1, R7.1
SIGOUT7: J15.P$1, J16.4, L8.1, R8.1
SIGOUT8: J17.P$1, J18.4, L9.1, R9.1
SIGOUT9: J19.P$1, J20.4, L10.1, R10.1
SIGOUT10: J21.P$1, J22.4, L11.1, R11.1
SIGOUT11: J23.P$1, J24.4, L12.1, R12.1
SIGOUT12: J25.P$1, J26.4, L13.1, R13.1
SIGOUT13: J27.P$1, J28.4, L14.1, R14.1
SIGOUT14: J29.P$1, J30.4, L15.1, R15.1
SIGOUT15: J31.P$1, J32.4, L16.1, R16.1
SIGOUT16: J33.P$1, J34.4, L17.1, R17.1
SIGOUT17: J35.P$1, J36.4, L18.1, R18.1
SIGOUT18: J37.P$1, J38.4, L19.1, R19.1
SIGOUT19: J39.P$1, J40.4, L20.1, R20.1
SIGOUT20: J41.P$1, J42.4, L21.1, R21.1
SIGOUT21: J43.P$1, J44.4, L22.1, R22.1
SIGOUT22: J45.P$1, J46.4, L23.1, R23.1
SIGOUT23: J47.P$1, J48.4, L24.1, R24.1
SIGOUT24: J49.P$1, J50.4, L25.1, R25.1
VCOAX: C2.1, C3.1, C4.1, J2.3, U2.6, U2.7, U2.8
VCOAX1: C5.1, C7.1, C8.1, J4.3, U1.6, U1.7, U1.8
VCOAX2: C9.1, C11.1, C12.1, J6.3, U3.6, U3.7, U3.8
VCOAX3: C13.1, C15.1, C16.1, J8.3, U4.6, U4.7, U4.8
VCOAX4: C17.1, C19.1, C20.1, J10.3, U5.6, U5.7, U5.8
VCOAX5: C21.1, C23.1, C24.1, J12.3, U6.6, U6.7, U6.8
VCOAX6: C25.1, C27.1, C28.1, J14.3, U7.6, U7.7, U7.8
VCOAX7: C29.1, C31.1, C32.1, J16.3, U8.6, U8.7, U8.8
VCOAX8: C33.1, C35.1, C36.1, J18.3, U9.6, U9.7, U9.8
VCOAX9: C37.1, C39.1, C40.1, J20.3, U10.6, U10.7, U10.8
VCOAX10: C41.1, C43.1, C44.1, J22.3, U11.6, U11.7, U11.8
VCOAX11: C45.1, C47.1, C48.1, J24.3, U12.6, U12.7, U12.8
VCOAX12: C49.1, C51.1, C52.1, J26.3, U13.6, U13.7, U13.8
VCOAX13: C53.1, C55.1, C56.1, J28.3, U14.6, U14.7, U14.8
VCOAX14: C57.1, C59.1, C60.1, J30.3, U15.6, U15.7, U15.8
VCOAX15: C61.1, C63.1, C64.1, J32.3, U16.6, U16.7, U16.8
VCOAX16: C65.1, C67.1, C68.1, J34.3, U17.6, U17.7, U17.8
VCOAX17: C69.1, C71.1, C72.1, J36.3, U18.6, U18.7, U18.8
VCOAX18: C73.1, C75.1, C76.1, J38.3, U19.6, U19.7, U19.8
VCOAX19: C77.1, C79.1, C80.1, J40.3, U20.6, U20.7, U20.8
VCOAX20: C81.1, C83.1, C84.1, J42.3, U21.6, U21.7, U21.8
VCOAX21: C85.1, C87.1, C88.1, J44.3, U22.6, U22.7, U22.8
VCOAX22: C89.1, C91.1, C92.1, J46.3, U23.6, U23.7, U23.8
VCOAX23: C93.1, C95.1, C96.1, J48.3, U24.6, U24.7, U24.8
VCOAX24: C97.1, C99.1, C100.1, J50.3, U25.6, U25.7, U25.8
VRAW: C1.1, J2.2, U2.1, U2.2
VRAW1: C6.1, J4.2, U1.1, U1.2
VRAW2: C10.1, J6.2, U3.1, U3.2
VRAW3: C14.1, J8.2, U4.1, U4.2
VRAW4: C18.1, J10.2, U5.1, U5.2
VRAW5: C22.1, J12.2, U6.1, U6.2
VRAW6: C26.1, J14.2, U7.1, U7.2
VRAW7: C30.1, J16.2, U8.1, U8.2
VRAW8: C34.1, J18.2, U9.1, U9.2
VRAW9: C38.1, J20.2, U10.1, U10.2
VRAW10: C42.1, J22.2, U11.1, U11.2
VRAW11: C46.1, J24.2, U12.1, U12.2
VRAW12: C50.1, J26.2, U13.1, U13.2
VRAW13: C54.1, J28.2, U14.1, U14.2
VRAW14: C58.1, J30.2, U15.1, U15.2
VRAW15: C62.1, J32.2, U16.1, U16.2
VRAW16: C66.1, J34.2, U17.1, U17.2
VRAW17: C70.1, J36.2, U18.1, U18.2
VRAW18: C74.1, J38.2, U19.1, U19.2
VRAW19: C78.1, J40.2, U20.1, U20.2
VRAW20: C82.1, J42.2, U21.1, U21.2
VRAW21: C86.1, J44.2, U22.1, U22.2
VRAW22: C90.1, J46.2, U23.1, U23.2
VRAW23: C94.1, J48.2, U24.1, U24.2
VRAW24: C98.1, J50.2, U25.1, U25.2

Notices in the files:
coax-adapter/coax-adapter-protected/headstage-64-coax-adapter.sch:
LICENSE: CC BY-NC-SA 4.0
headstage-64.sch:
LICENSE: CERN OHL v1.2
